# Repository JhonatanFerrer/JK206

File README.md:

<h2 align="Left"> English </h2>

This project consists of a mechanical ortolinear keyboard design that is capable of being used for both a macropad and a 50% keyboard.

This is achieved through a modular design PCB that can be used by itself to mount a macropad with up to 20 keys (5 of them can be exchanged for encoders); while with three PCBs you can mount a keyboard with up to 60 keys (3 of them can be encoders)

The source code of the keyboard was written in CircuitPython using the <a href="http://kmkfw.io/">KMK firmware</a>, the microcontroller used is the Raspberry Pi Pico.

If you want to build your own JK206, go to the guide, where there will be the step-by-step to assemble and configure it

<strong>Note:</strong> If you just want to assemble your own JK206 and don't plan to modify anything of the PCB design, you don't need to touch the KiCAD files, directly use the Gerbers as the guide says

<h2 align="Left"> Español </h2>

Este proyecto consiste en un diseño de teclado mecánico ortolineal que es capaz de utilizarse tanto para un macropad como para un teclado 50%. 

Esto se consigue mediante una PCB de diseño modular que se puede usar por si misma para montar un macropad de hasta 20 teclas (5 de ellas se pueden cambiar por encoders); mientras que con tres PCBs se puede montar un teclado de hasta 60 teclas (3 de ellas pueden ser encoders)

El código fuente del teclado fue escrito en CircuitPython haciendo uso del <a href="http://kmkfw.io/">firmware KMK</a>, el microcontrolador utilizado es el Raspberry Pi Pico.

Si quieres armar tu propio JK206, entra en la guía, donde estará el paso a paso para ensamblarlo y configurarlo 

<strong>Nota:</strong> Si solo quieres montar tu propio JK206 y no piensan modificar nada del diseño de la PCB , no necesitas tocar los archivos de KiCAD, usa directamente los Gerbers como dice la guía

<h1 align="Left"> Photos / Fotos </h1>

These photos are from a prototype version of the project, the final version features some minor changes / Estas fotos son de una versión prototipo del proyecto, la versión final presenta algunos cambios menores

<h1 align="Left"> ToDo </h1>

1. Finish the Spanish guide and make the English guide. / Terminar la guía en español y hacer la guía en inglés
   
2. Make the keyboard compatible with <a href="https://peg.software/">Peg</a> / Hacer el teclado compatible con <a href="https://peg.software/">Peg</a>

3. Add the possibility to insert UNICODE characters (this causes keyboard crashes) / Agregar la posibilidad de insertar caracteres UNICODE (esto causa crasheos en el teclado)
  
4. Ensure that when the keyboard is connected, the computer does not display its storage, or at least displays it under the name JK206 / Hacer que al ser conectado el teclado, el computador no muestre su almacenamiento, o al menos lo muestre bajo el nombre Jk206

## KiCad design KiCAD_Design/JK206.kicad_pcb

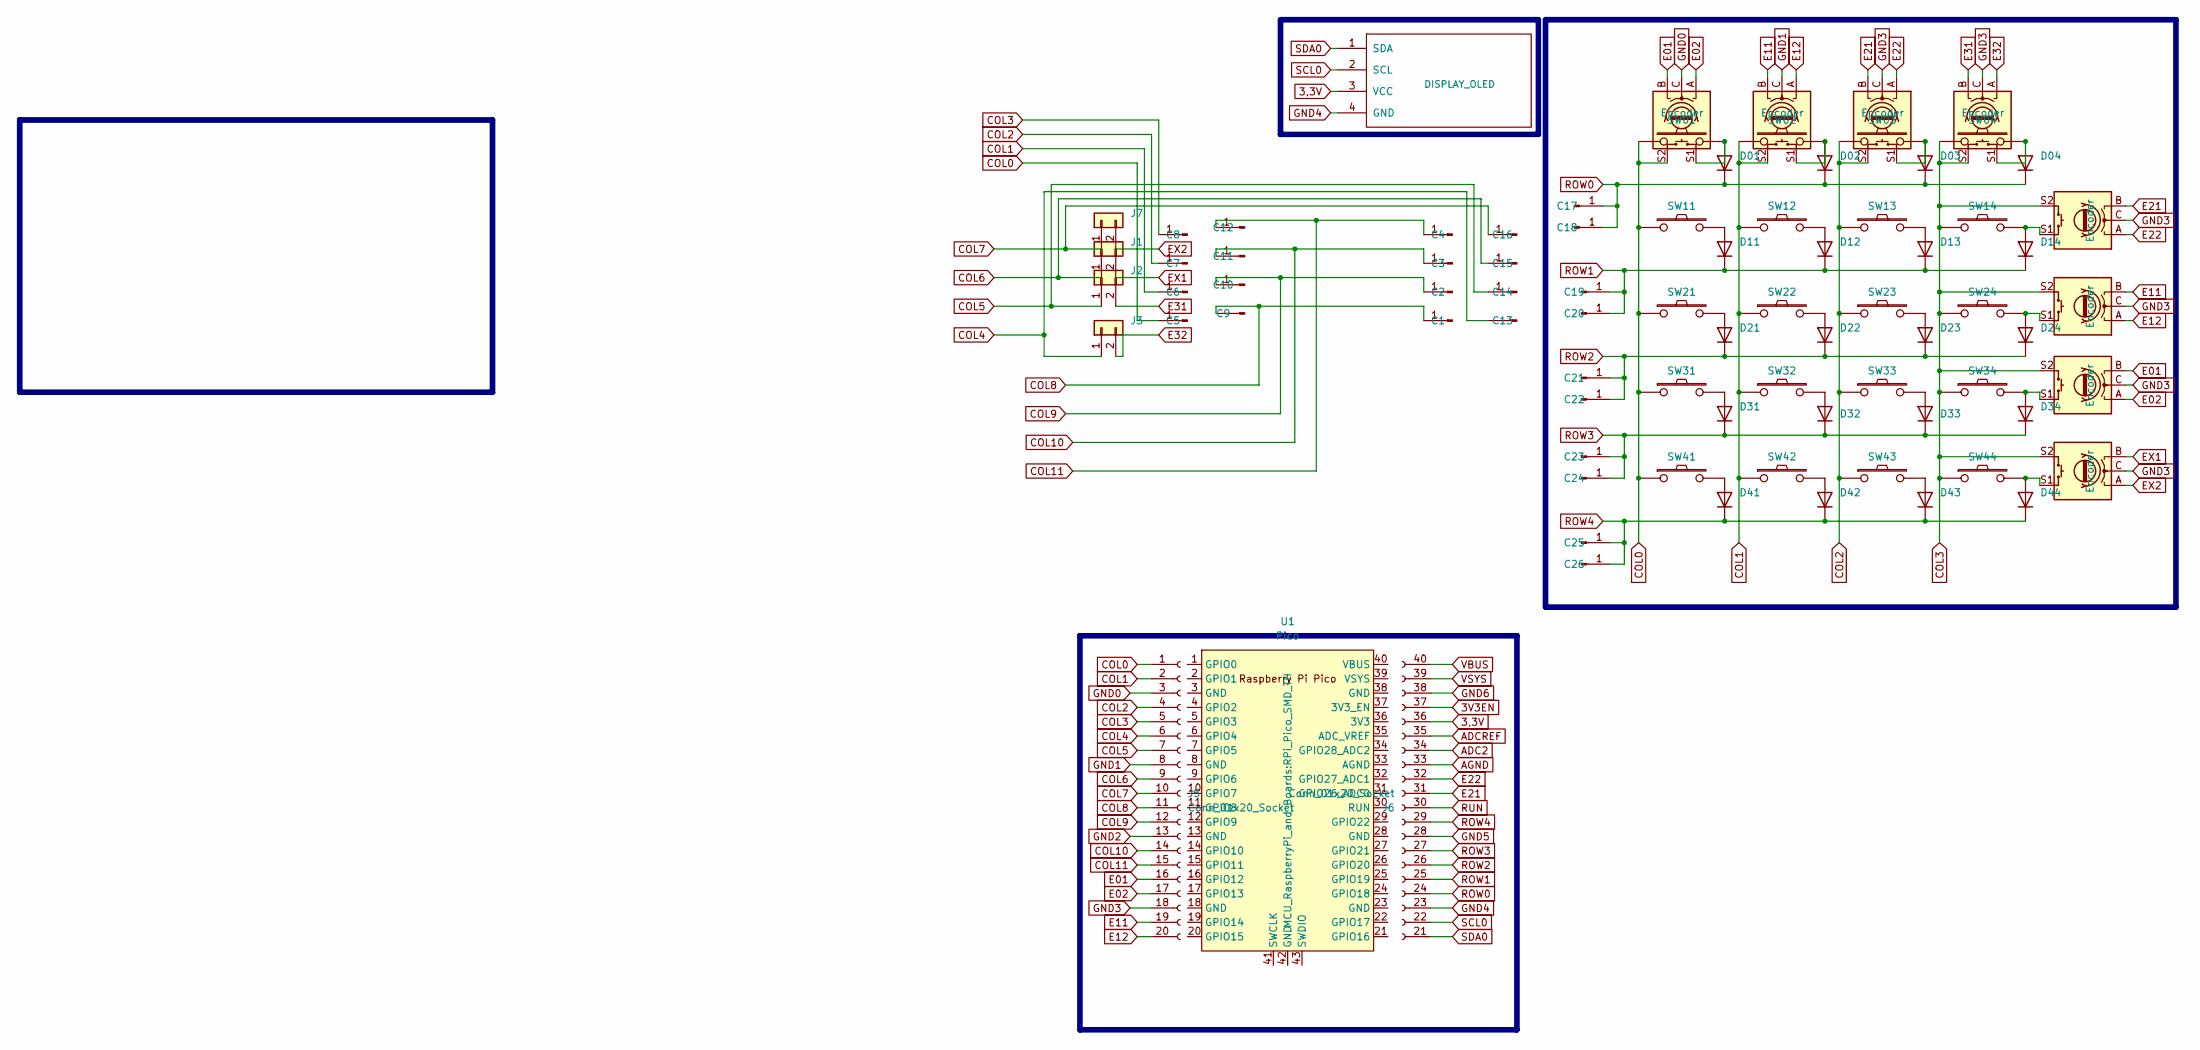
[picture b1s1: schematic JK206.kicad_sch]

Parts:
C1, C2, C3, C4, C5, C6, C7, C8, C9, C10, C11, C12, C13, C14, C15, C16: Conn_01x01_Pin; Pin_D1.0mm_L10.0mm
C17, C18, C19, C20, C21, C22, C23, C24, C25, C26: Conn_01x01_Pin; SolderWire-0.1sqmm_1x01_D0.4mm_OD1mm
D01, D02, D03, D04, D11, D12, D13, D14, D21, D22, D23, D24, D31, D32, D33, D34, D41, D42, D43, D44: 1N4148; D_DO-35_SOD27_P7.62mm_Horizontal
J1, J2, J3, J7: Connector_Generic_Conn_01x02; PinSocket_1x02_P2.54mm_Vertical
J5, J6: Conn_01x20_Socket; PinSocket_1x20_P2.54mm_Vertical
OL1: DISPLAY_OLED; 128x64OLED
SW01, SW02, SW03, SW04, SW11, SW12, SW13, SW14, SW21, SW22, SW23, SW24, SW31, SW32, SW33, SW34, SW41, SW42, SW43, SW44: SW_PUSH; CherryMX_Hotswap
SW5, SW18, SW19, SW20, SW25, SW26, SW27, SW28: Encoder; RotaryEncoder_Alps_EC11E-Switch_Vertical_H20mm
U1: Pico; RPi_Pico_SMD_TH

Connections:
3,3V: J6.36 (Pin_16), OL1.3 (VCC); also elsewhere on the board
3V3EN: J6.37 (Pin_17)
ADC2: J6.34 (Pin_14)
ADCREF: J6.35 (Pin_15)
AGND: J6.33 (Pin_13)
COL0: C5.1, J5.1, SW01.1, SW5.S2, SW11.1, SW21.1, SW31.1, SW41.1
COL1: C6.1, J5.2, SW02.1, SW12.1, SW18.S2, SW22.1, SW32.1, SW42.1
COL2: C7.1, J5.4, SW03.1, SW13.1, SW19.S2, SW23.1, SW33.1, SW43.1
COL3: C8.1, J5.5, SW04.1, SW14.1, SW20.S2, SW24.1, SW25.S2, SW26.S2, SW27.S2, SW28.S2, SW34.1, SW44.1
COL4: C13.1, J3.1, J5.6
COL5: C14.1, J2.1, J5.7
COL6: C15.1, J1.1, J5.9
COL7: C16.1, J5.10, J7.1
COL8: C1.1, C9.1, J5.11
COL9: C2.1, C10.1, J5.12
COL10: C3.1, C11.1, J5.14
COL11: C4.1, C12.1, J5.15
E01: J5.16, SW5.B, SW27.B
E02: J5.17, SW5.A, SW27.A
E11: J5.19, SW18.B, SW26.B
E12: J5.20, SW18.A, SW26.A
E21: J6.31 (Pin_11), SW19.B, SW25.B
E22: J6.32 (Pin_12), SW19.A, SW25.A
E31: J2.2, SW20.B
E32: J3.2, SW20.A
EX1: J1.2, SW28.B
EX2: J7.2, SW28.A
GND0: J5.3, SW5.C
GND1: J5.8, SW18.C
GND2: J5.13
GND3: J5.18, SW19.C, SW20.C, SW25.C, SW26.C, SW27.C, SW28.C
GND4: J6.23 (Pin_3), OL1.4 (GND); also elsewhere on the board
GND5: J6.28 (Pin_8)
GND6: J6.38 (Pin_18)
unnamed: D01.2 (A), SW01.2, SW5.S1
unnamed: D02.2 (A), SW02.2, SW18.S1
unnamed: D03.2 (A), SW03.2, SW19.S1
unnamed: D04.2 (A), SW04.2, SW20.S1
unnamed: D11.2 (A), SW11.2
unnamed: D12.2 (A), SW12.2
unnamed: D13.2 (A), SW13.2
unnamed: D14.2 (A), SW14.2, SW25.S1
unnamed: D21.2 (A), SW21.2
unnamed: D22.2 (A), SW22.2
unnamed: D23.2 (A), SW23.2
unnamed: D24.2 (A), SW24.2, SW26.S1
unnamed: D31.2 (A), SW31.2
unnamed: D32.2 (A), SW32.2
unnamed: D33.2 (A), SW33.2
unnamed: D34.2 (A), SW27.S1, SW34.2
unnamed: D41.2 (A), SW41.2
unnamed: D42.2 (A), SW42.2
unnamed: D43.2 (A), SW43.2
unnamed: D44.2 (A), SW28.S1, SW44.2
ROW0: C17.1, C18.1, D01.1 (K), D02.1 (K), D03.1 (K), D04.1 (K), J6.24 (Pin_4)
ROW1: C19.1, C20.1, D11.1 (K), D12.1 (K), D13.1 (K), D14.1 (K), J6.25 (Pin_5)
ROW2: C21.1, C22.1, D21.1 (K), D22.1 (K), D23.1 (K), D24.1 (K), J6.26 (Pin_6)
ROW3: C23.1, C24.1, D31.1 (K), D32.1 (K), D33.1 (K), D34.1 (K), J6.27 (Pin_7)
ROW4: C25.1, C26.1, D41.1 (K), D42.1 (K), D43.1 (K), D44.1 (K), J6.29 (Pin_9)
RUN: J6.30 (Pin_10)
SCL0: J6.22 (Pin_2), OL1.2 (SCL); also elsewhere on the board
SDA0: J6.21 (Pin_1), OL1.1 (SDA); also elsewhere on the board
VBUS: J6.40 (Pin_20)
VSYS: J6.39 (Pin_19)

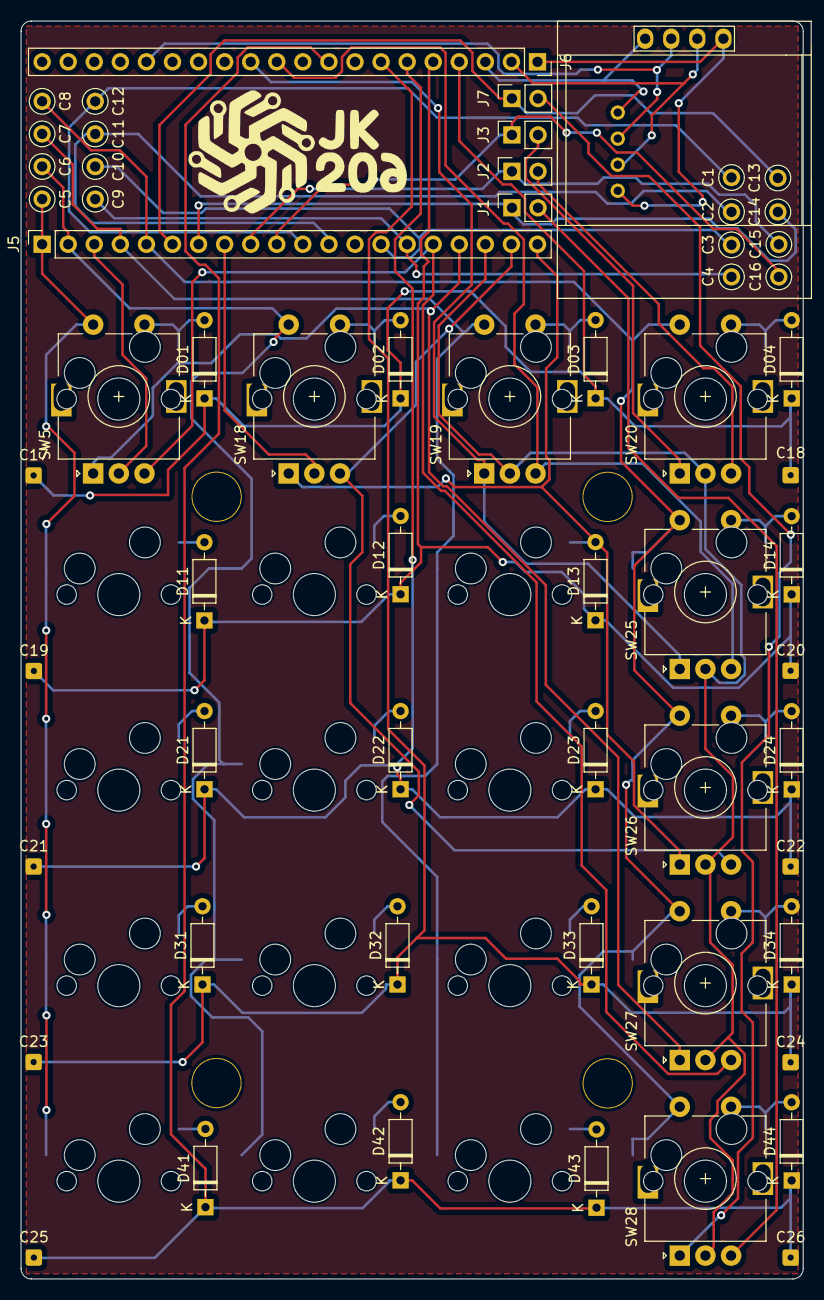
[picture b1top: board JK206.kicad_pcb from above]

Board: 2 copper layers, 76.2 x 122.6 mm, 82 parts (0 on the bottom side), 54 nets.

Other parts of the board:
OL1#2: DISPLAY_OLED; 128x64OLED

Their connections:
3,3V: OL1#2.2 (SCL); also elsewhere on the board
GND4: OL1#2.1 (SDA); also elsewhere on the board
SCL0: OL1#2.3 (VCC); also elsewhere on the board
SDA0: OL1#2.4 (GND); also elsewhere on the board

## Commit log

2024-10-30 Added SymbolsWindows class
2025-01-14 imágenes agregadas a la guía de armado en español
2025-01-14 ajustes menores en la guía en español
2025-01-14 arreglando numeración en la guía de ensamble
2025-01-23 Guía de ensamble terminada (solo con montaje tipo sandwich)
2025-01-23 cambio en el título de la guía
2025-01-30 guía completada (creo)
2025-01-30 ajustes menores
2025-01-31 ajustes en las tablas
2025-01-31 ajustes varios.md
